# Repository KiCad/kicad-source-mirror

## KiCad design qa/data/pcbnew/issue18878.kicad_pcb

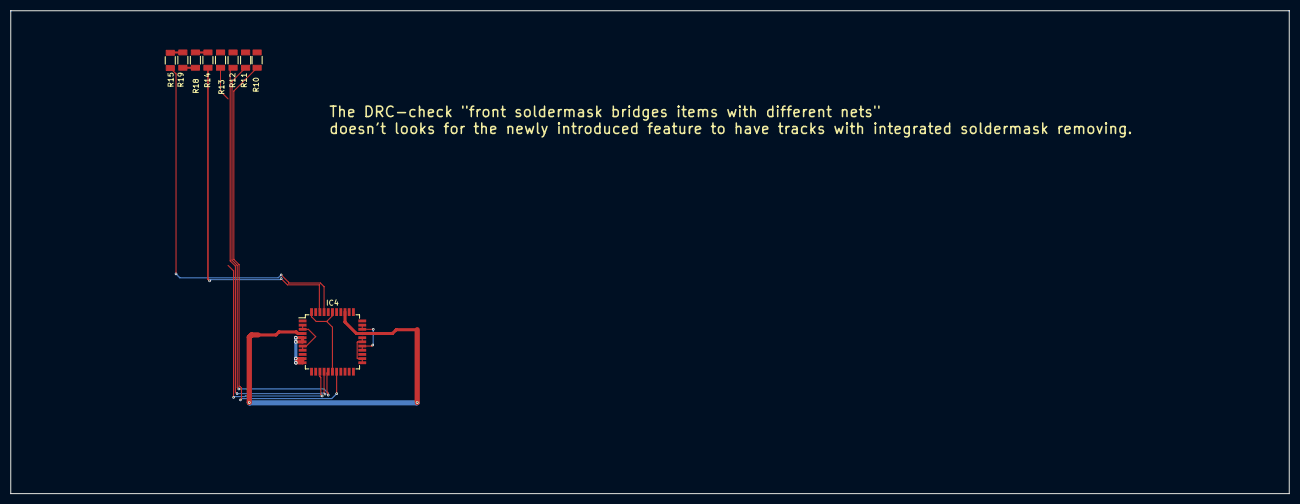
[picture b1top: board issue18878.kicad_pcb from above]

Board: 2 copper layers, 244.4 x 92.3 mm, 9 parts (0 on the bottom side), 15 nets.

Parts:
IC4: TMC261C-PA; TQFP-44_10x10mm_P0.8mm
R10, R11, R12, R13, R14, R15: 1k; R_1206_3216Metric
R18, R19: 100k; R_1206_3216Metric

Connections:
+3V3: R18.1, R19.1
IO_P1_0: IC4.42 (STEP), R14.2
IO_P1_1: IC4.41 (DIR), R15.2
unnamed: IC4.17 (GND), IC4.39 (GND), IC4.44 (GND)
unnamed: IC4.2 (OA1), IC4.3 (OA1), IC4.7 (OA1), IC4.8 (OA1)
unnamed: IC4.5 (OA2), IC4.6 (OA2), IC4.10 (OA2), IC4.11 (OA2)
unnamed: IC4.26 (OB1), IC4.27 (OB1), IC4.31 (OB1), IC4.32 (OB1)
unnamed: IC4.23 (OB2), IC4.24 (OB2), IC4.28 (OB2), IC4.29 (OB2)
unnamed: IC4.4 (VS/VSA/VSB), IC4.30 (VS/VSA/VSB), IC4.36 (VS/VSA/VSB)
unnamed: R14.1, R18.2
unnamed: R15.1, R19.2
SPI1_MISO: IC4.15 (SDI), R12.2
SPI1_MOSI: IC4.14 (SDO), R13.2
SPI1_SCK: IC4.16 (SCK), R11.2
SPI1_SSEL: IC4.18 (~CS), R10.2
